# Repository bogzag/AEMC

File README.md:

# AEMC PROJECT:v:
The task is to create a meteo station (schematic, layout,code,hardware). 

Please upload your work in the correct section and add comments to avoid confusion between team members

Mention urgent tasks here and mark them with :exclamation:

Mark wrong info like this  ~~This info wrong my man~~

### Team members:sleeping:

@bogzag

@ClaudiaGitH

@alexandruf98

### Pt curs/proiect
(https://join.skype.com/lMuimAnFgpZ3?fbclid=IwAR00U5oWaqc2DzT4iKskiz9u4dI-uODVIiYZsmZv1TnuRMnrCDzAk37EaNk)

:exclamation: Layout+Code

### $ Lista de cumparaturi:
https://docs.google.com/spreadsheets/d/1xGkr67w3PWWBnmwl580I28Ox6pwAhuXMNzGf5ZXCvtU/edit?usp=drive_web&ouid=117811896005838952029

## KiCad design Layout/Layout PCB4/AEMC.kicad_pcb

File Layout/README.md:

# Layout for AEMC PROJECT, done in 

## Task list:yum:

- De finalizat partea cu senzorul de umiditate si amplificarea
- De ingrosat putin mai mult traseele (acum sunt 0.8 mm)

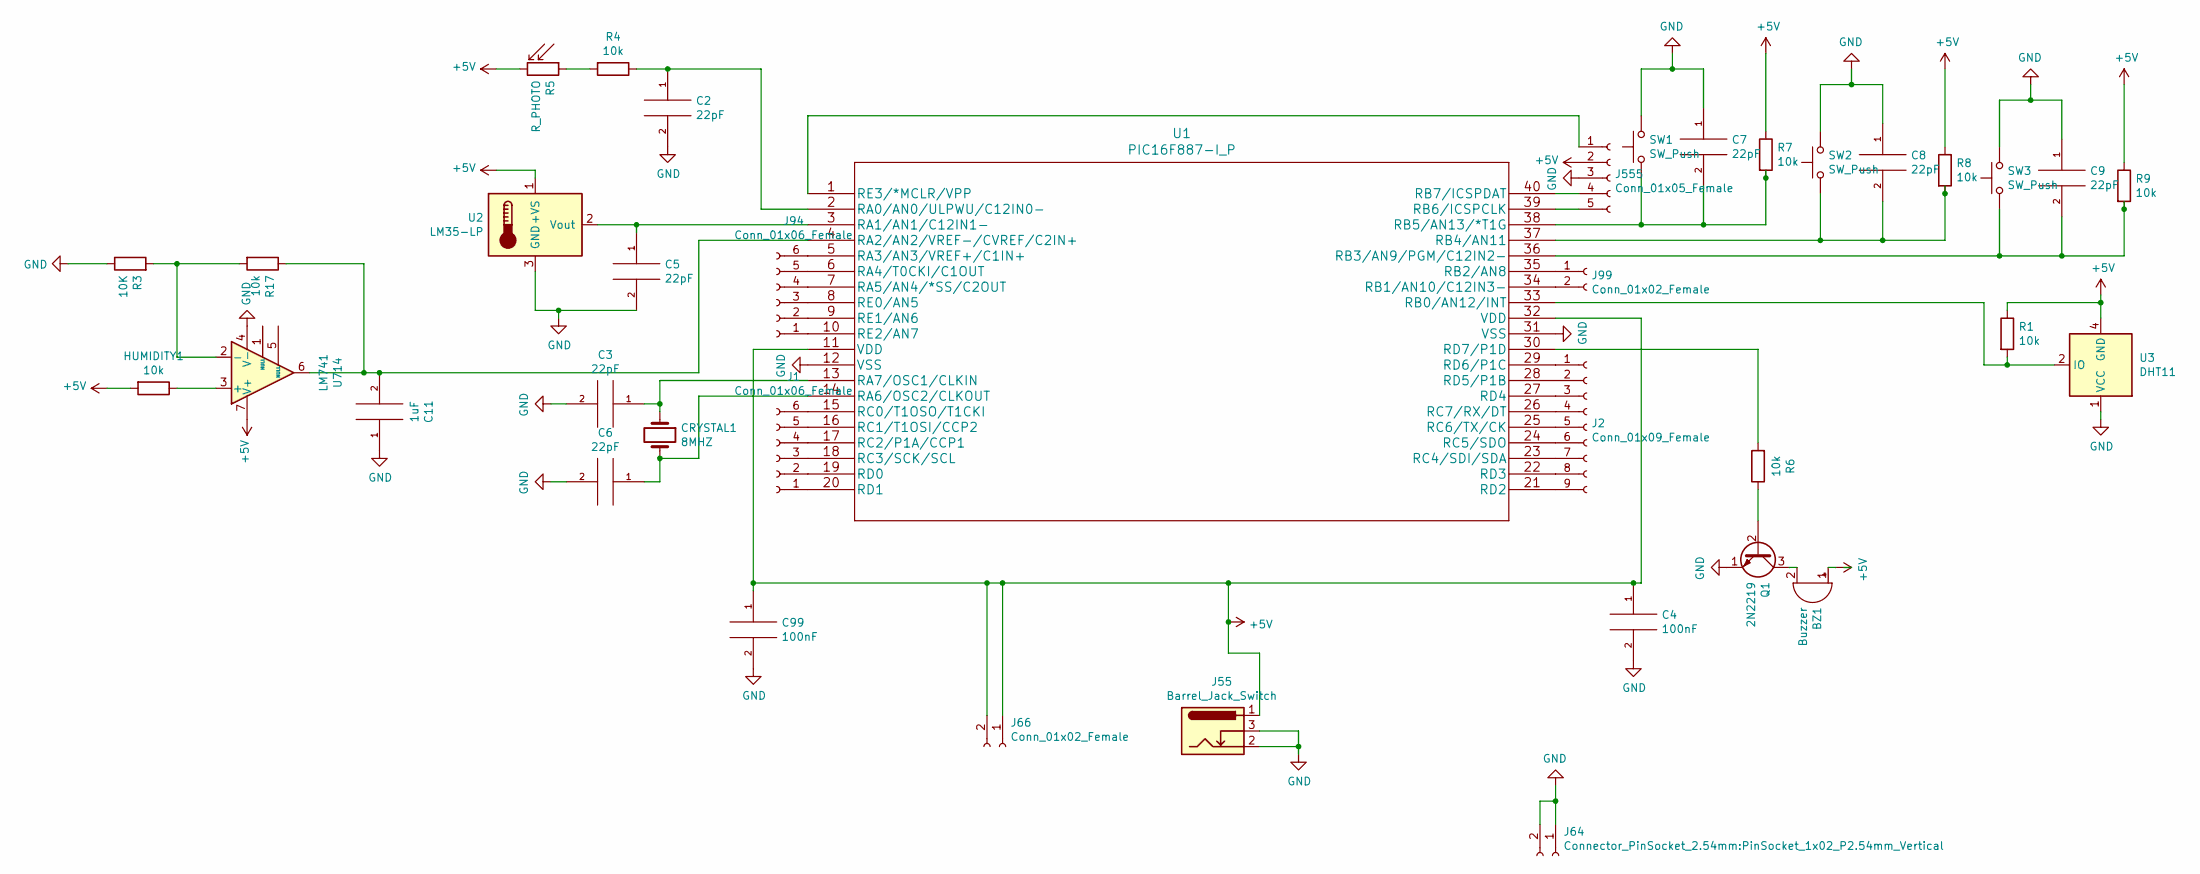
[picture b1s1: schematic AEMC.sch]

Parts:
BZ1: Buzzer; Buzzer_TDK_PS1240P02BT_D12.2mm_H6.5mm
C2, C3, C5, C6, C7, C8, C9: 22pF; C_Disc_D4.7mm_W2.5mm_P5.00mm
C4, C99: 100nF; C_Disc_D4.7mm_W2.5mm_P5.00mm
C11: 1uF; C_Disc_D4.7mm_W2.5mm_P5.00mm
CRYSTAL1: 8MHZ; Resonator-2Pin_W6.0mm_H3.0mm
HUMIDITY1: 10k; PinSocket_1x02_P2.54mm_Vertical
J1, J94: Conn_01x06_Female; PinSocket_1x06_P2.54mm_Vertical
J2: Conn_01x09_Female; PinSocket_1x09_P2.54mm_Vertical
J55: Barrel_Jack_Switch; BarrelJack_CUI_PJ-102AH_Horizontal
J64: Connector_PinSocket_2.54mm:PinSocket_1x02_P2.54mm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; PinSocket_1x02_P2.54mm_Vertical
J66, J99: Conn_01x02_Female; PinSocket_1x02_P2.54mm_Vertical
J555: Conn_01x05_Female; PinSocket_1x05_P2.54mm_Vertical
Q1: 2N2219; TO-39-3
R1, R4, R6, R7, R8, R9, R17: 10k; R_Axial_DIN0204_L3.6mm_D1.6mm_P5.08mm_Horizontal
R3: 10K; R_Axial_DIN0204_L3.6mm_D1.6mm_P5.08mm_Horizontal
R5: R_PHOTO; R_Axial_DIN0204_L3.6mm_D1.6mm_P5.08mm_Horizontal
SW1, SW2, SW3: SW_Push; SW_CW_GPTS203211B
U1: PIC16F887-I_P; PIC16F887-I&slash_P
U2: LM35-LP; TO-39-3
U3: DHT11; Aosong_DHT11_5.5x12.0_P2.54mm
U714: LM741; UA741CP

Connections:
+5V: BZ1.1 (-), C4.1, C99.1, HUMIDITY1.2, J55.1, J66.1, J66.2, J555.2, R1.1, R5.2, R7.1, R8.1, R9.1, U1.11 (VDD), U1.32 (VDD), U2.1 (+VS), U3.4 (GND), U714.7 (V+)
GND: C2.2, C3.2, C4.2, C5.2, C6.2, C7.1, C8.1, C9.1, C11.1, C99.2, J55.2, J55.3, J64.1, J64.2, J555.3, Q1.1 (E), R3.1, SW1.2, SW2.2, SW3.2, U1.12 (VSS), U1.31 (VSS), U2.3 (GND), U3.1 (VCC), U714.4 (V-)
unnamed: BZ1.2 (+), Q1.3 (C)
unnamed: C2.1, R4.1, U1.2 (RA0/AN0/ULPWU/C12IN0-)
unnamed: C3.1, CRYSTAL1.1, U1.13 (RA7/OSC1/CLKIN)
unnamed: C5.1, U1.3 (RA1/AN1/C12IN1-), U2.2 (Vout)
unnamed: C6.1, CRYSTAL1.2, U1.14 (RA6/OSC2/CLKOUT)
unnamed: C7.2, R7.2, SW1.1, U1.38 (RB5/AN13/*T1G)
unnamed: C8.2, R8.2, SW2.1, U1.37 (RB4/AN11)
unnamed: C9.2, R9.2, SW3.1, U1.36 (RB3/AN9/PGM/C12IN2-)
unnamed: C11.2, R17.1, U1.4 (RA2/AN2/VREF-/CVREF/C2IN+), U714.6
unnamed: HUMIDITY1.1, U714.3 (+)
unnamed: J1.1, U1.20 (RD1)
unnamed: J1.2, U1.19 (RD0)
unnamed: J1.3, U1.18 (RC3/SCK/SCL)
unnamed: J1.4, U1.17 (RC2/P1A/CCP1)
unnamed: J1.5, U1.16 (RC1/T1OSI/CCP2)
unnamed: J1.6, U1.15 (RC0/T1OSO/T1CKI)
unnamed: J2.1, U1.29 (RD6/P1C)
unnamed: J2.2, U1.28 (RD5/P1B)
unnamed: J2.3, U1.27 (RD4)
unnamed: J2.4, U1.26 (RC7/RX/DT)
unnamed: J2.5, U1.25 (RC6/TX/CK)
unnamed: J2.6, U1.24 (RC5/SDO)
unnamed: J2.7, U1.23 (RC4/SDI/SDA)
unnamed: J2.8, U1.22 (RD3)
unnamed: J2.9, U1.21 (RD2)
unnamed: J94.1, U1.10 (RE2/AN7)
unnamed: J94.2, U1.9 (RE1/AN6)
unnamed: J94.3, U1.8 (RE0/AN5)
unnamed: J94.4, U1.7 (RA5/AN4/*SS/C2OUT)
unnamed: J94.5, U1.6 (RA4/T0CKI/C1OUT)
unnamed: J94.6, U1.5 (RA3/AN3/VREF+/C1IN+)
unnamed: J99.1, U1.35 (RB2/AN8)
unnamed: J99.2, U1.34 (RB1/AN10/C12IN3-)
unnamed: J555.1, U1.1 (RE3/*MCLR/VPP)
unnamed: J555.4, U1.40 (RB7/ICSPDAT)
unnamed: J555.5, U1.39 (RB6/ICSPCLK)
unnamed: Q1.2 (B), R6.1
unnamed: R1.2, U1.33 (RB0/AN12/INT), U3.2 (IO)
unnamed: R4.2, R5.1
unnamed: R6.2, U1.30 (RD7/P1D)
unnamed: R3.2, R17.2, U714.2 (-)

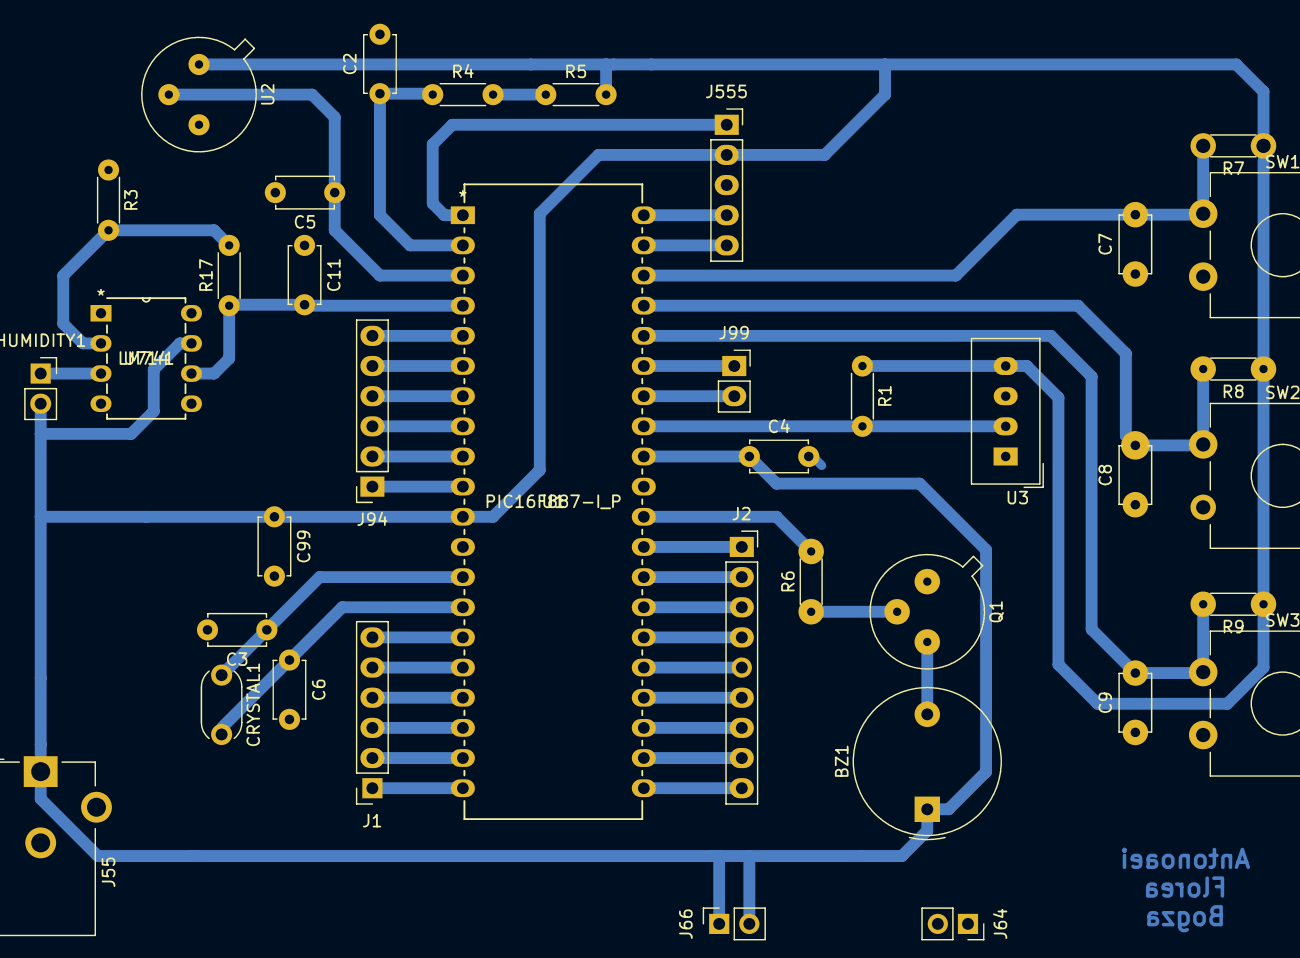
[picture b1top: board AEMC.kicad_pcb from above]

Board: 2 copper layers, 38 parts (0 on the bottom side), 43 nets.

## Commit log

2020-03-11 Add files via upload
    Updated at lab
2020-03-16 Schema dupa meeting-ul de pe skype
2020-03-17 Add files via upload
    update:ICSP & routat pini
2020-03-17 Rename lcd.c to Code/lcd.c
2020-03-17 Rename main.c to Code/main.c
2020-03-17 Rename DHT11.IDX to Libraries/DHT11.IDX
2020-03-17 Add files via upload
    schematic changes-DONE
2020-03-21 /librarie/PIC16LF877
    Librarie pentru PIC16LF877
2020-03-21 Librarie PIC16F887
    Librarie PIC16F887 pentru KiCad
2020-03-22 Add files via upload
    I am dat lui Adi schema sa verifice, nu mi a rasp, dar momentan e oki cat sa facem layout
    Trebuie calculate rezistentele
2020-03-23 Add files via upload
    versiunea1
2020-03-23 Add files via upload
    updates sensors
2020-03-23 test sim aemc
2020-03-23 v2.2
2020-03-23 Create RealTimeClock
2020-03-23 SIMULARE CARE MERGE FMM
2020-03-23 Schematic for PCB
2020-03-24 Create LM35
2020-03-24 test lm35
2020-03-24 main
2020-03-24 Layout cu trasee trase 24/03/2020
2020-03-24 Liprarii pentru footprints (KiCad)
2020-03-24 Librarie KiCad (footprins)
2020-03-24 pic16.zip
2020-03-24 Add files via upload
    includes functions for dht11
2020-03-31 test lm 35
2020-03-31 lm35 functional
2020-04-07 Modificare trasee, compactare componente
    Prima incercare de imprimare pe foaie
2020-04-07 Add files via upload
    cod i2c+buzzer, kinda working, needs lcd.c file from the lab
2020-04-08 lm+fotorez functional +dht
2020-04-14 Update components footprints
2020-04-14 dhtfunctional
    12h dht
2020-04-28 Layout (sper sa fie bun si sa fie cel final)
    - Mici modificari pe ici pe colo
    - Am marit latimea traseelor (1mm)
    - Am marit pad-urile
    - Am stat si am verificat daca layout-ul corespunde cu dimensiunile componentelor
    - Am folosit multimetrul cumparat... sa masor rezistenta fotorezistorului in functie de intensitatea luminii
    - Am realizat practic imprimarea layout-ului pe placuta de cupru... (6-7 aproximativ)
2020-05-16 Create RTCfunctional.txt
    Trebuie adaugata si alarma
2020-05-18 senzor umiditate analogica

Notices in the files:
parts and their libraries:
Copyright 2016 Accelerated Designs. All rights reserved.
